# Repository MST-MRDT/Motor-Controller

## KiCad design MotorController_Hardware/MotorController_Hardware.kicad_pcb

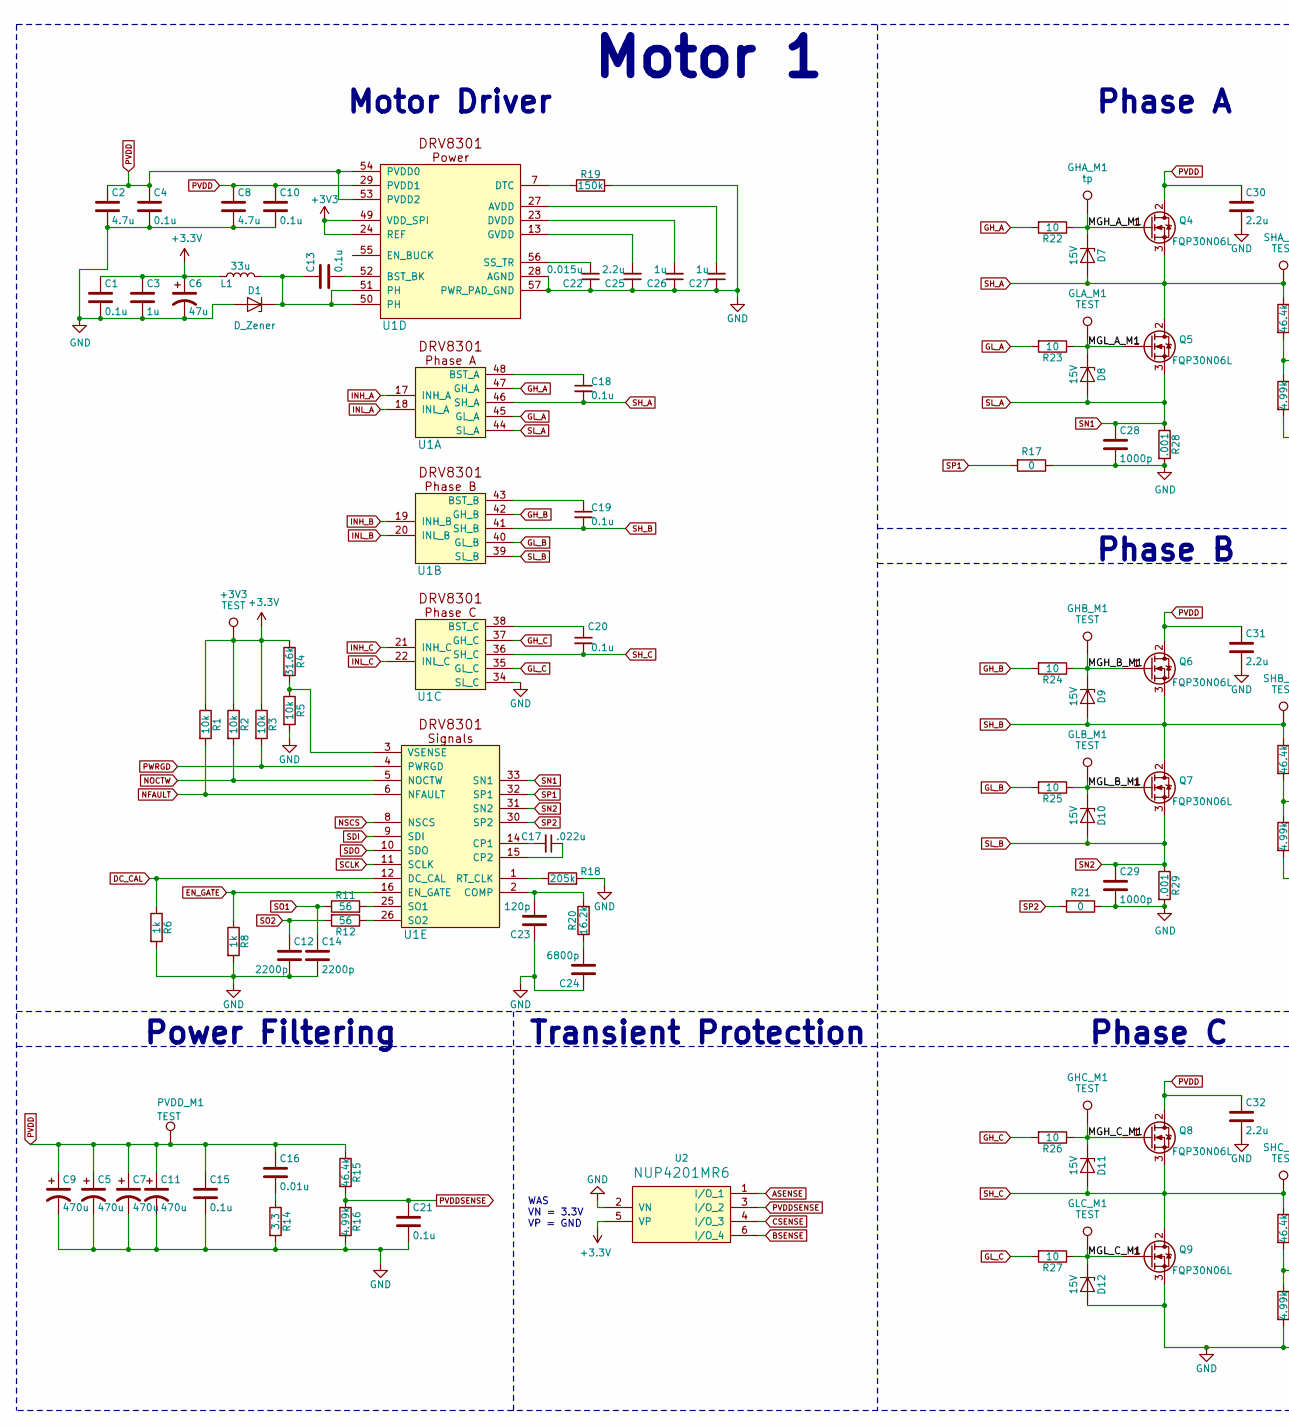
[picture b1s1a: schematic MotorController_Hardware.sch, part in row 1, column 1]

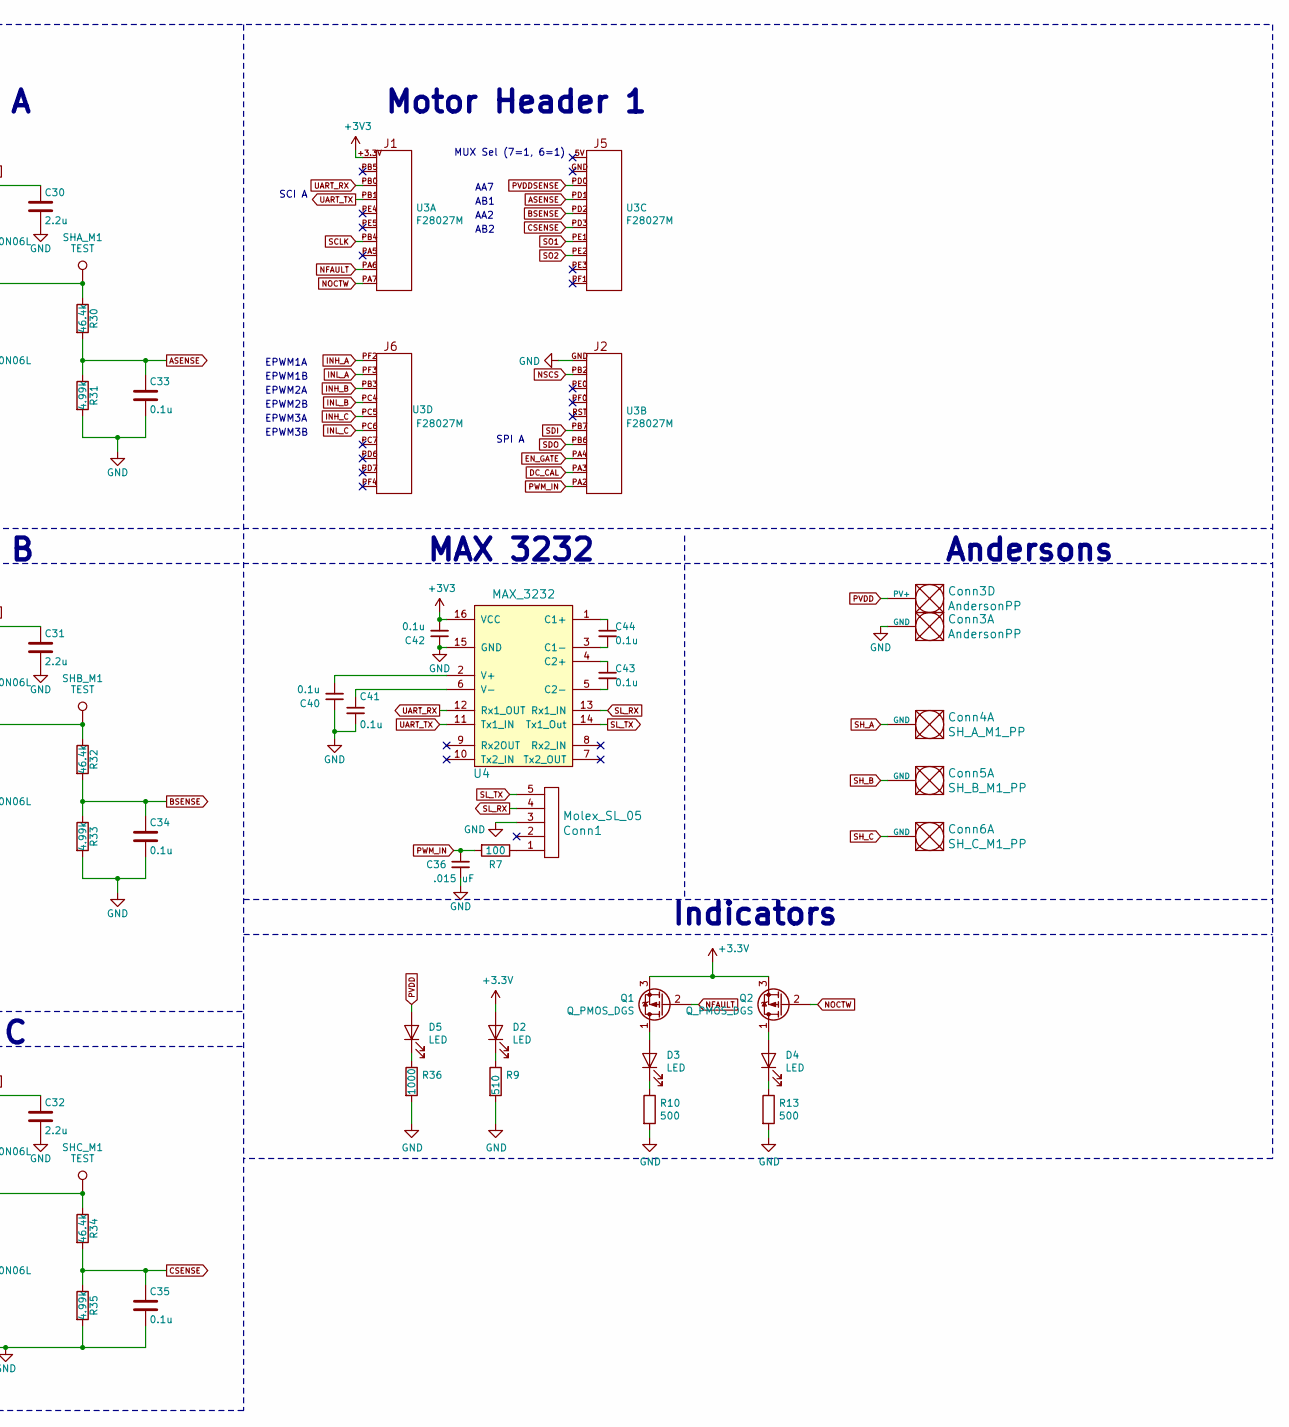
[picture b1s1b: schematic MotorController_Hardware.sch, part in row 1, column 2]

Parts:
+3V3: TEST; Via_.6mm
C1, C4, C10, C13, C15, C18, C19, C20, C21, C33, C34, C35, C40, C41, C42, C43, C44: 0.1u; C_0603_1608Metric_Pad1.05x0.95mm_HandSolder
C2, C8: 4.7u; C_0603_1608Metric_Pad1.05x0.95mm_HandSolder
C3, C26, C27: 1u; C_0603_1608Metric_Pad1.05x0.95mm_HandSolder
C5, C7, C9, C11: 470u; CP_Radial_D12.5mm_P5.00mm
C6: 47u; CP_Radial_D6.3mm_P2.50mm
C12, C14: 2200p; C_0603_1608Metric_Pad1.05x0.95mm_HandSolder
C16: 0.01u; C_0603_1608Metric_Pad1.05x0.95mm_HandSolder
C17: .022u; C_0603_1608Metric_Pad1.05x0.95mm_HandSolder
C22: 0.015u; C_0603_1608Metric_Pad1.05x0.95mm_HandSolder
C23: 120p; C_0603_1608Metric_Pad1.05x0.95mm_HandSolder
C24: 6800p; C_0603_1608Metric_Pad1.05x0.95mm_HandSolder
C25, C30, C31, C32: 2.2u; C_0603_1608Metric_Pad1.05x0.95mm_HandSolder
C28, C29: 1000p; C_0603_1608Metric_Pad1.05x0.95mm_HandSolder
C36: .015 uF; C_0603_1608Metric_Pad1.05x0.95mm_HandSolder
Conn1: Molex_SL_05; MOLEX_SL_05_Horizontal
Conn3: AndersonPP; Anderson_2_Horizontal_Stacked
Conn4: SH_A_M1_PP; Anderson_1_Horizontal
Conn5: SH_B_M1_PP; Anderson_1_Horizontal
Conn6: SH_C_M1_PP; Anderson_1_Horizontal
D1: D_Zener; D_0603_1608Metric_Pad1.05x0.95mm_HandSolder
D2, D3, D4, D5: LED; L_0603_1608Metric_Pad1.05x0.95mm_HandSolder
D7, D8, D9, D10, D11, D12: 15V; D_SOD-123
GHA_M1: tp; Via_.6mm
GHB_M1: TEST; Via_.6mm
GHC_M1: TEST; Via_.6mm
GLA_M1: TEST; Via_.6mm
GLB_M1: TEST; Via_.6mm
GLC_M1: TEST; Via_.6mm
L1: 33u; DR74_330_R
PVDD_M1: TEST; Via_.6mm
Q1, Q2: Q_PMOS_DGS; SOT-23_Handsoldering
Q4, Q5, Q6, Q7, Q8, Q9: FQP30N06L; TO-220-3_Horizontal_Reversed_NoHole
R1, R2, R3, R5: 10k; R_0603_1608Metric_Pad1.05x0.95mm_HandSolder
R4: 31.6k; R_0603_1608Metric_Pad1.05x0.95mm_HandSolder
R6, R8: 1k; R_0603_1608Metric_Pad1.05x0.95mm_HandSolder
R7: 100; R_0603_1608Metric_Pad1.05x0.95mm_HandSolder
R9: 510; R_0603_1608Metric_Pad1.05x0.95mm_HandSolder
R10, R13: 500; R_0603_1608Metric_Pad1.05x0.95mm_HandSolder
R11, R12: 56; R_0603_1608Metric_Pad1.05x0.95mm_HandSolder
R14: 3.3; R_1206_3216Metric_Pad1.42x1.75mm_HandSolder
R15, R30, R32, R34: 46.4k; R_0603_1608Metric_Pad1.05x0.95mm_HandSolder
R16, R31, R33, R35: 4.99k; R_0603_1608Metric_Pad1.05x0.95mm_HandSolder
R17, R21: 0; R_0603_1608Metric_Pad1.05x0.95mm_HandSolder
R18: 205k; R_0603_1608Metric_Pad1.05x0.95mm_HandSolder
R19: 150k; R_0603_1608Metric_Pad1.05x0.95mm_HandSolder
R20: 16.2k; R_0603_1608Metric_Pad1.05x0.95mm_HandSolder
R22, R23, R24, R25, R26, R27: 10; R_0603_1608Metric_Pad1.05x0.95mm_HandSolder
R28, R29: .001; R_1206_3216Metric_Pad1.42x1.75mm_HandSolder
R36: 1000; R_0603_1608Metric_Pad1.05x0.95mm_HandSolder
SHA_M1: TEST; Via_.6mm
SHB_M1: TEST; Via_.6mm
SHC_M1: TEST; Via_.6mm
U1: DRV8301
U2: NUP4201MR6
U3: F28027M; F28027M_THT_TOP
U4: MAX_3232; SOIC_16_3.9x9.9mm_Pitch1.27mm

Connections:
/MGH_A_M1: D7.1 (K), GHA_M1.1, Q4.1 (G), R22.1
/MGH_B_M1: D9.1 (K), GHB_M1.1, Q6.1 (G), R24.1
/MGH_C_M1: D11.1 (K), GHC_M1.1, Q8.1 (G), R26.1
/MGL_A_M1: D8.1 (K), GLA_M1.1, Q5.1 (G), R23.1
/MGL_B_M1: D10.1 (K), GLB_M1.1, Q7.1 (G), R25.1
/MGL_C_M1: D12.1 (K), GLC_M1.1, Q9.1 (G), R27.1
ASENSE: C33.1, R30.2, R31.1, U2.1 (I/O_1), U3.PD1
BSENSE: C34.1, R32.2, R33.1, U2.6 (I/O_4), U3.PD2
CSENSE: C35.1, R34.2, R35.1, U2.4 (I/O_3), U3.PD3
DC_CAL: R6.1, U1.12 (DC_CAL), U3.PA3
EN_GATE: R8.1, U1.16 (EN_GATE), U3.PA4
GH_A: R22.2, U1.47 (GH_A)
GH_B: R24.2, U1.42 (GH_B)
GH_C: R26.2, U1.37 (GH_C)
GL_A: R23.2, U1.45 (GL_A)
GL_B: R25.2, U1.40 (GL_B)
GL_C: R27.2, U1.35 (GL_C)
INH_A: U1.17 (INH_A), U3.PF2
INH_B: U1.19 (INH_B), U3.PB3
INH_C: U1.21 (INH_C), U3.PC5
INL_A: U1.18 (INL_A), U3.PF3
INL_B: U1.20 (INL_B), U3.PC4
INL_C: U1.22 (INL_C), U3.PC6
NFAULT: Q1.2 (G), R1.2, U1.6 (NFAULT), U3.PA6
NOCTW: Q2.2 (G), R2.2, U1.5 (NOCTW), U3.PA7
NSCS: U1.8 (NSCS), U3.PB2
unnamed: C13.1, D1.1 (K), L1.2, U1.50 (PH), U1.51 (PH)
unnamed: C13.2, U1.52 (BST_BK)
unnamed: C16.2, R14.1
unnamed: C17.1, U1.15 (CP2)
unnamed: C17.2, U1.14 (CP1)
unnamed: C18.1, U1.48 (BST_A)
unnamed: C19.1, U1.43 (BST_B)
unnamed: C20.1, U1.38 (BST_C)
unnamed: C22.2, U1.56 (SS_TR)
unnamed: C23.2, R20.2, U1.2 (COMP)
unnamed: C24.2, R20.1
unnamed: C25.2, U1.13 (GVDD)
unnamed: C26.2, U1.23 (DVDD)
unnamed: C27.2, U1.27 (AVDD)
unnamed: C40.2, U4.2 (V+)
unnamed: C41.1, U4.6 (V-)
unnamed: C43.1, U4.4 (C2+)
unnamed: C43.2, U4.5 (C2-)
unnamed: C44.1, U4.1 (C1+)
unnamed: C44.2, U4.3 (C1-)
unnamed: Conn1.1, R7.1
unnamed: D2.1 (K), R9.1
unnamed: D3.1 (K), R10.1
unnamed: D3.2 (A), Q1.1 (D)
unnamed: D4.1 (K), R13.1
unnamed: D4.2 (A), Q2.1 (D)
unnamed: D5.1 (K), R36.1
unnamed: R4.2, R5.1, U1.3 (VSENSE)
unnamed: R11.2, U1.25 (SO1)
unnamed: R12.1, U1.26 (SO2)
unnamed: R18.1, U1.1 (RT_CLK)
unnamed: R19.1, U1.7 (DTC)
PVDD: C2.1, C4.1, C5.1, C7.1, C8.1, C9.1, C10.1, C11.1, C15.1, C16.1, C30.1, C31.1, C32.1, Conn3.4 (PV+), D5.2 (A), PVDD_M1.1, Q4.2 (D), Q6.2 (D), Q8.2 (D), R15.1, U1.29 (PVDD1), U1.53 (PVDD2), U1.54 (PVDD0)
PVDDSENSE: C21.1, R15.2, R16.1, U2.3 (I/O_2), U3.PD0
PWM_IN: C36.1, R7.2, U3.PA2
PWRGD: R3.2, U1.4 (PWRGD)
SCLK: U1.11 (SCLK), U3.PB4
SDI: U1.9 (SDI), U3.PB7
SDO: U1.10 (SDO), U3.PB6
SH_A: C18.2, Conn4.1 (GND), D7.2 (A), Q4.3 (S), Q5.2 (D), R30.1, SHA_M1.1, U1.46 (SH_A)
SH_B: C19.2, Conn5.1 (GND), D9.2 (A), Q6.3 (S), Q7.2 (D), R32.1, SHB_M1.1, U1.41 (SH_B)
SH_C: C20.2, Conn6.1 (GND), D11.2 (A), Q8.3 (S), Q9.2 (D), R34.1, SHC_M1.1, U1.36 (SH_C)
SL_A: C28.1, D8.2 (A), Q5.3 (S), R28.1, U1.33 (SN1), U1.44 (SL_A)
SL_B: C29.1, D10.2 (A), Q7.3 (S), R29.1, U1.31 (SN2), U1.39 (SL_B)
SL_RX: Conn1.4, U4.13 (Rx1_IN)
SL_TX: Conn1.5, U4.14 (Tx1_Out)
SO1: C14.1, R11.1, U3.PE1
SO2: C12.1, R12.2, U3.PE2
SP1: R17.2, U1.32 (SP1)
SP2: R21.2, U1.30 (SP2)
UART_RX: U3.PB0, U4.12 (Rx1_OUT)
UART_TX: U3.PB1, U4.11 (Tx1_IN)

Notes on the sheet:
Power Filtering
Transient Protection
Motor Driver
Phase A
Phase B
Phase C
Indicators
MAX 3232
Motor Header 1
Motor 1
Andersons
MUX Sel (7=1, 6=1)
AA7
AB1
AA2
AB2
SCI A
SPI A
EPWM3B
EPWM3A
EPWM2B
EPWM2A
EPWM1B
EPWM1A
WAS VN = 3.3V VP = GND

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
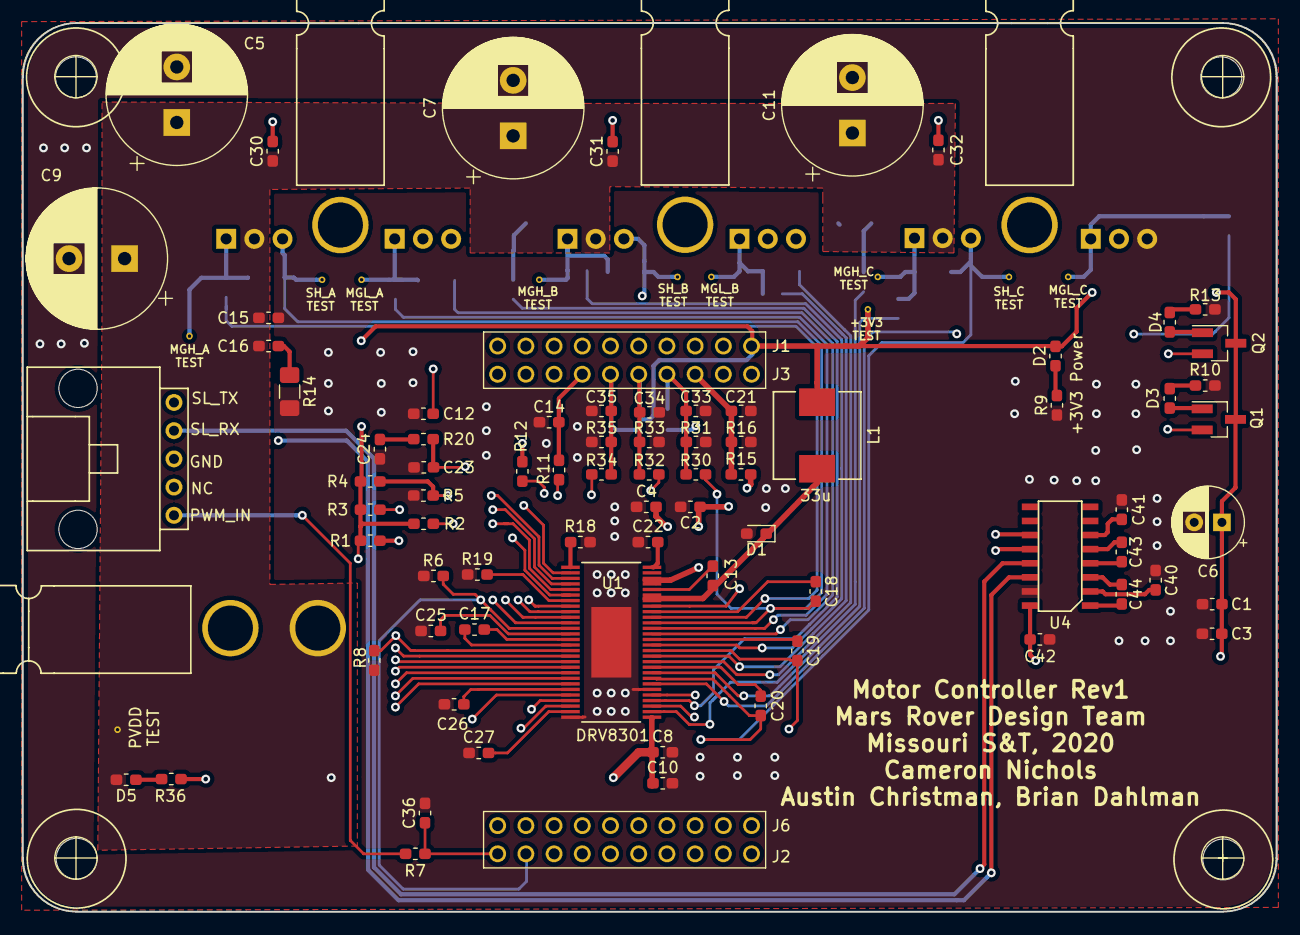
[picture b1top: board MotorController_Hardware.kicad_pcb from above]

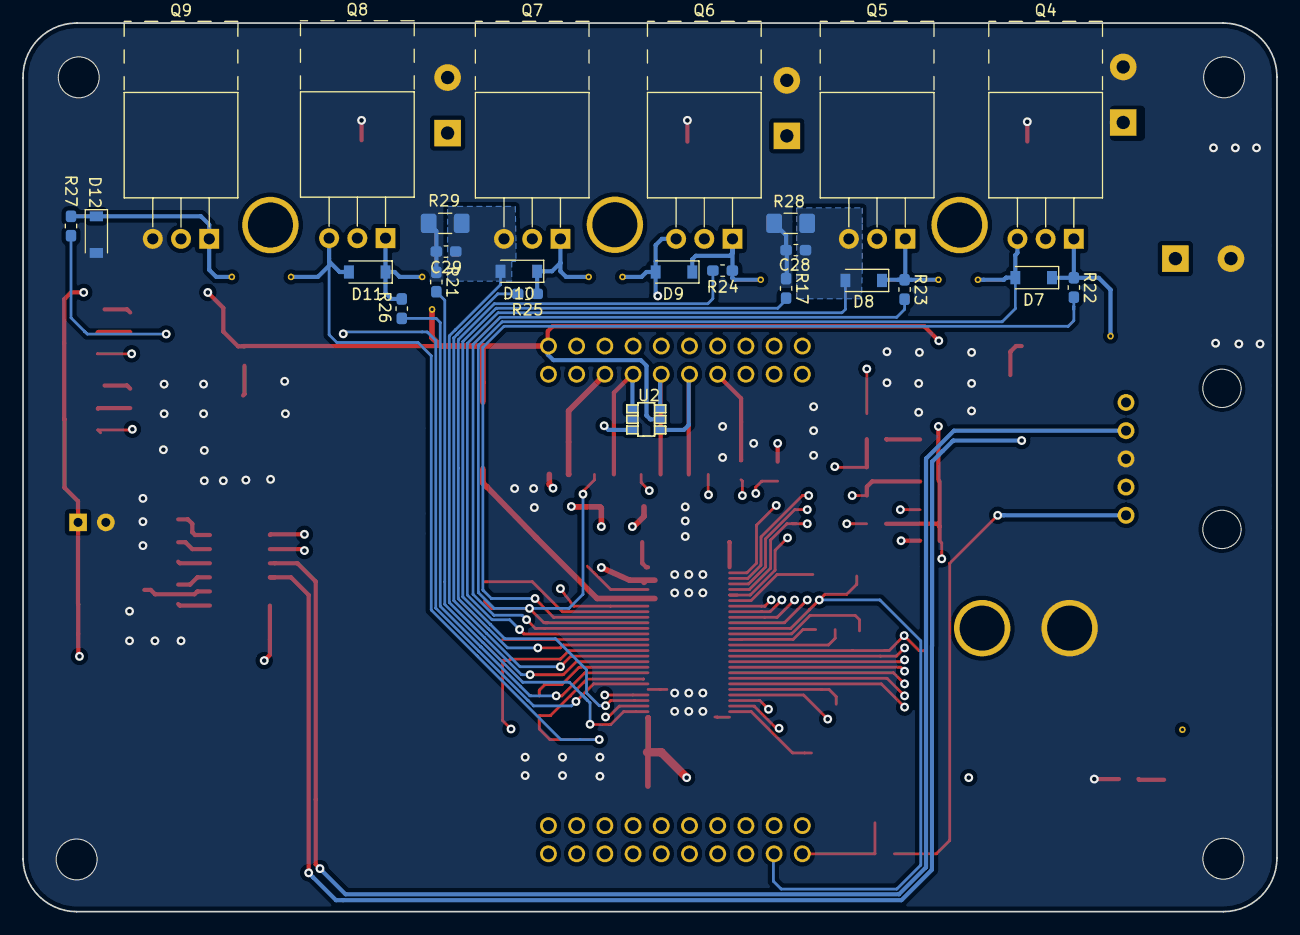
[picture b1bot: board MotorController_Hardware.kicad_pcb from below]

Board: 4 copper layers, 112.9 x 80.0 mm, 117 parts (25 on the bottom side), 80 nets.

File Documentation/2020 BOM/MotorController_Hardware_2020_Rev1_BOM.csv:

Id,Designator,Package,Quantity,Designation,Supplier and ref,
1,G***,Zenith_Logo_30mm,1,LOGO,,
2,G***,Wifi_Power_Net_5mmX6mm,1,LOGO,,
3,"REF**,REF**,REF**,REF**",4_40_Hole_Corner,4,4_40_Hole,,
4,U1,DRV8301,1,DRV8301,https://www.digikey.com/products/en?keywords=296-29433-1-ND,https://www.newark.com/texas-instruments/drv8301dcar/motor-d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
5,"C1,C4,C10,C13,C15,C18,C19,C20,C21,C33,C34,C35,C40,C41,C42,C43,C44",C_0603_1608Metric_Pad1.05x0.95mm_HandSolder,17,0.1u,https://www.newark.com/avx/06035c104jat2a/ceramic-capacitor-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,
6,"C2,C8",C_0603_1608Metric_Pad1.05x0.95mm_HandSolder,2,4.7u,https://www.digikey.com/products/en?keywords=490-10751-1-ND,
7,"C3,C26,C27",C_0603_1608Metric_Pad1.05x0.95mm_HandSolder,3,1u,https://www.newark.com/avx/06035c104jat2a/ceramic-capacitor-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,
8,"C5,C7,C9,C11",CP_Radial_D12.5mm_P5.00mm,4,470u,https://www.newark.com/panasonic/eca-1jhg471/aluminum-electr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,
9,C6,CP_Radial_D6.3mm_P2.50mm,1,47u,https://www.newark.com/panasonic/eca-1hm470/aluminum-electro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,
10,"C12,C14",C_0603_1608Metric_Pad1.05x0.95mm_HandSolder,2,2200p,https://www.newark.com/kemet/c0603c222k5ractu/ceramic-capaci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,
11,C16,C_0603_1608Metric_Pad1.05x0.95mm_HandSolder,1,0.01u,https://www.newark.com/tdk/cga3e2x7r1h103k080ae/cap-0-01-f-5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,
12,C17,C_0603_1608Metric_Pad1.05x0.95mm_HandSolder,1,.022u,https://www.newark.com/vishay/vj0603y223jxacw1bc/cap-0-022-f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,
13,C22,C_0603_1608Metric_Pad1.05x0.95mm_HandSolder,1,0.015u,https://www.newark.com/vishay/vj0603y153kxacw1bc/cap-0-015-f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,
14,C23,C_0603_1608Metric_Pad1.05x0.95mm_HandSolder,1,120p,https://www.newark.com/avx/06035a121jat2a/ceramic-capacitor-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,
15,C24,C_0603_1608Metric_Pad1.05x0.95mm_HandSolder,1,6800p,https://www.newark.com/kemet/c0603c682j5gactu/cap-mlcc-c0g-6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,
16,"C25,C30,C31,C32",C_0603_1608Metric_Pad1.05x0.95mm_HandSolder,4,2.2u,https://www.newark.com/taiyo-yuden/umk107bbj225ka-t/capacito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,
17,"C28,C29",C_0603_1608Metric_Pad1.05x0.95mm_HandSolder,2,1000p,https://www.newark.com/avx/06035c102kat2a/ceramic-capacitor-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,
18,C36,C_0603_1608Metric_Pad1.05x0.95mm_HandSolder,1,.015 uF,https://www.newark.com/vishay/vj0603y153kxacw1bc/cap-0-015-f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,
19,Conn1,MOLEX_SL_05_Horizontal,1,Molex_SL_05,,
20,Conn3,Anderson_2_Horizontal_Stacked,1,AndersonPP,,
21,Conn4,Anderson_1_Horizontal,1,SH_A_M1_PP,,
22,Conn5,Anderson_1_Horizontal,1,SH_B_M1_PP,,
23,Conn6,Anderson_1_Horizontal,1,SH_C_M1_PP,,
24,"D2,D3,D4,D5",L_0603_1608Metric_Pad1.05x0.95mm_HandSolder,4,LED,https://www.newark.com/vishay/vlmg1300-gs08/led-yellow-green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,
25,"D7,D8,D9,D10,D11,D12",D_SOD-123,6,15V,https://www.newark.com/on-semiconductor/mmsz4684t1g/zener-di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,
26,L1,DR74_330_R,1,33u,https://www.newark.com/eaton-coiltronics/dr74-330-r/inductor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,
27,"Q1,Q2",SOT-23_Handsoldering,2,Q_PMOS_DGS,https://www.digikey.com/products/en?keywords=SSM3J338RLFCT-ND,
28,"Q4,Q5,Q6,Q7,Q8,Q9",TO-220-3_Horizontal_Reversed_NoHole,6,FQP30N06L,https://www.digikey.com/products/en?keywords=FQP30N06L,
29,"R1,R2,R3,R5",R_0603_1608Metric_Pad1.05x0.95mm_HandSolder,4,10k,https://www.newark.com/multicomp/mcwr06x1002ftl/surface-moun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,
30,R4,R_0603_1608Metric_Pad1.05x0.95mm_HandSolder,1,31.6k,https://www.newark.com/vishay/crcw040231k6fked/res-thick-fil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,
31,"R6,R8",R_0603_1608Metric_Pad1.05x0.95mm_HandSolder,2,1k,https://www.newark.com/vishay/crcw06031k00fkea/res-thick-fil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,
32,R7,R_0603_1608Metric_Pad1.05x0.95mm_HandSolder,1,100,https://www.newark.com/yageo/rc0603fr-07100rl/res-thick-film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,
33,R9,R_0603_1608Metric_Pad1.05x0.95mm_HandSolder,1,510,https://www.newark.com/vishay/crcw0603510rfkea/res-thick-fil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,
34,"R10,R13",R_0603_1608Metric_Pad1.05x0.95mm_HandSolder,2,500,https://www.newark.com/vishay/crcw0603510rfkea/res-thick-fil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,
35,"R11,R12",R_0603_1608Metric_Pad1.05x0.95mm_HandSolder,2,56,https://www.newark.com/vishay/crcw060356r0jnea/res-thick-fil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,
36,R14,R_1206_3216Metric_Pad1.42x1.75mm_HandSolder,1,3.3,https://www.newark.com/vishay/crcw12063r30jnea/res-thick-fil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,
37,"R15,R30,R32,R34",R_0603_1608Metric_Pad1.05x0.95mm_HandSolder,4,46.4k,https://www.digikey.com/product-detail/en/yageo/RT0603BRD074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,
38,"R16,R31,R33,R35",R_0603_1608Metric_Pad1.05x0.95mm_HandSolder,4,4.99k,https://www.digikey.com/product-detail/en/yageo/RT0603BRD074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,
39,R18,R_0603_1608Metric_Pad1.05x0.95mm_HandSolder,1,205k,https://www.newark.com/vishay/crcw0603205kfkea/res-thick-fil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,
40,R19,R_0603_1608Metric_Pad1.05x0.95mm_HandSolder,1,150k,https://www.newark.com/panasonic/erj-3ekf1503v/res-thick-fil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,
41,R20,R_0603_1608Metric_Pad1.05x0.95mm_HandSolder,1,16.2k,https://www.newark.com/panasonic/erj-3ekf1622v/res-thick-fil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,
42,"R22,R23,R24,R25,R26,R27",R_0603_1608Metric_Pad1.05x0.95mm_HandSolder,6,10,https://www.newark.com/vishay/crcw060310r0fkeahp/res-aec-q20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,
43,"R28,R29",R_1206_3216Metric_Pad1.42x1.75mm_HandSolder,2,0.001,https://www.digikey.com/product-detail/en/stackpole-electron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,
44,U2,NUP4201MR6,1,NUP4201MR6,https://www.digikey.com/product-detail/en/diodes-incorporate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,
45,U4,SOIC_16_3.9x9.9mm_Pitch1.27mm,1,MAX_3232,https://www.digikey.com/product-detail/en/texas-instruments/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,
46,"+3V3,GHB_M1,GHC_M1,GLA_M1,GLB_M1,GLC_M1,PVDD_M1,SHA_M1,SHB_M1,SHC_M1",Via_.6mm,10,TEST,,
47,GHA_M1,Via_.6mm,1,tp,,
48,D1,D_0603_1608Metric_Pad1.05x0.95mm_HandSolder,1,D_Zener,,
49,"R17,R21",R_0603_1608Metric_Pad1.05x0.95mm_HandSolder,2,0,https://www.newark.com/vishay/crcw06030000z0eahp/res-thick-f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,
50,U3,F28027M_THT_TOP,1,F28027M,,
51,R36,R_0603_1608Metric_Pad1.05x0.95mm_HandSolder,1,1000,https://www.newark.com/vishay/crcw06031k00fkea/surface-mount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,

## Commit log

2019-09-30 Schematic finished and footprints assigned
2019-10-05 high level layout
2019-10-05 PCB layout: In progress
2019-10-11 Work done on PCB layout
2019-10-13 Finished PCB layout
2019-10-13 Silkscreens added
2019-10-20 WORKING ON ORDERING
2019-11-07 BOM update

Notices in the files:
parts and their libraries:
Copyright 2016 Accelerated Designs. All rights reserved.
